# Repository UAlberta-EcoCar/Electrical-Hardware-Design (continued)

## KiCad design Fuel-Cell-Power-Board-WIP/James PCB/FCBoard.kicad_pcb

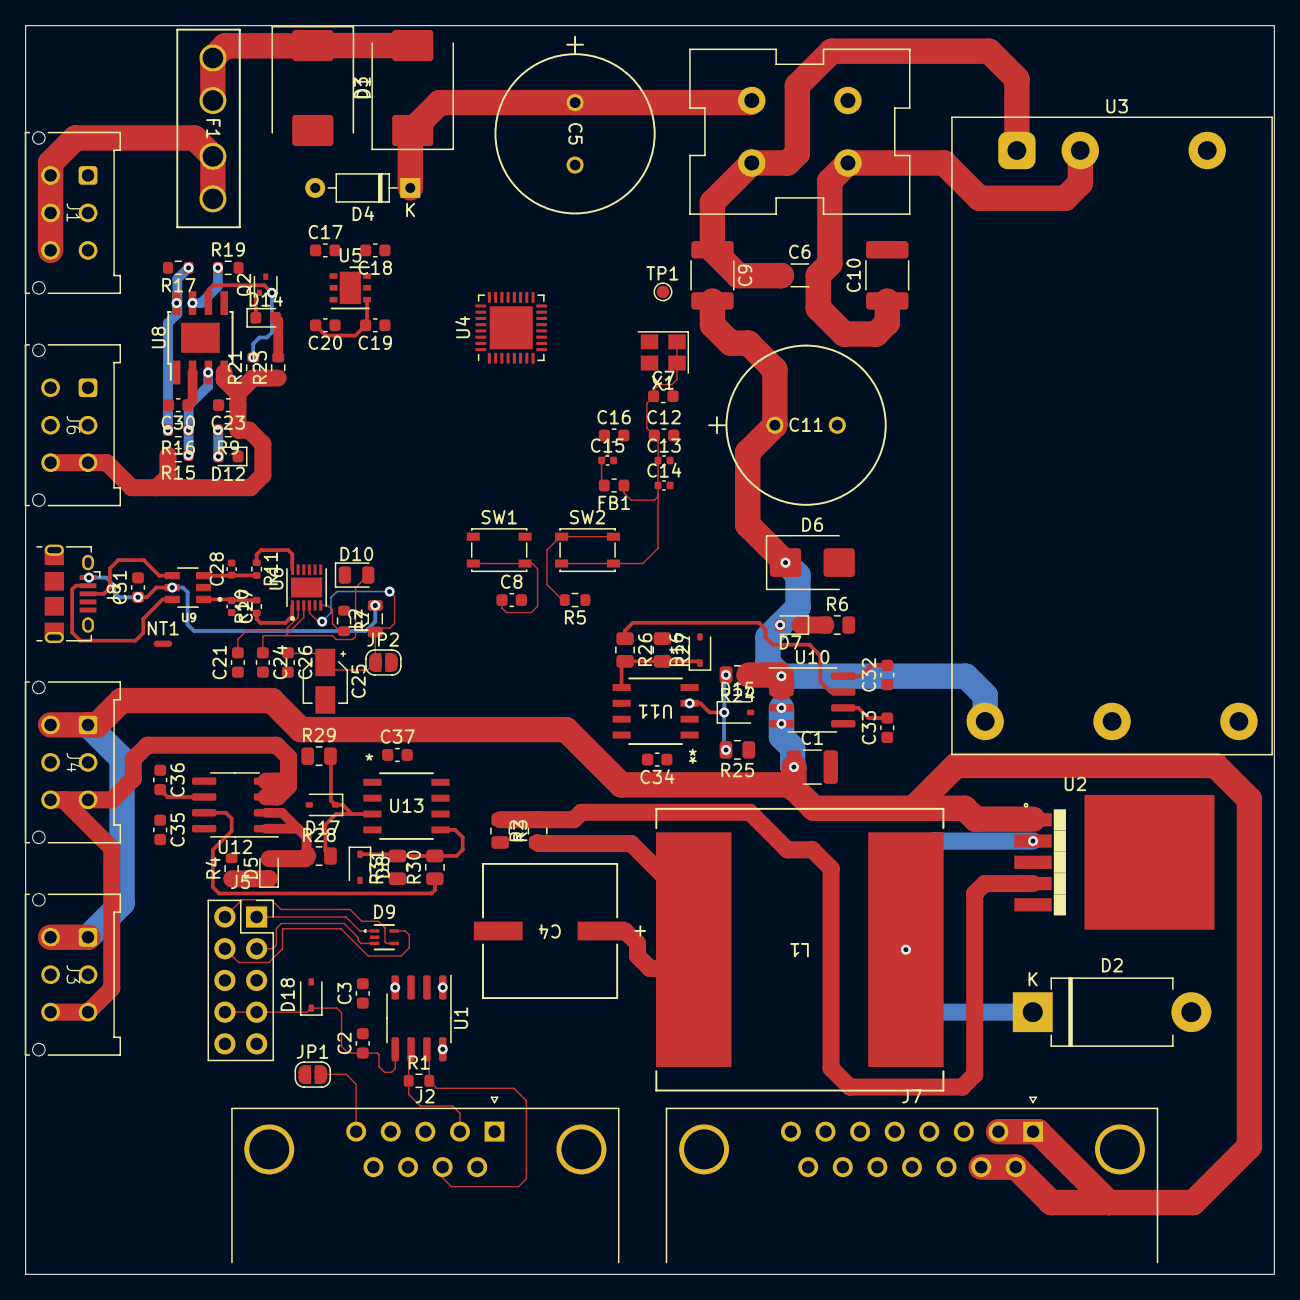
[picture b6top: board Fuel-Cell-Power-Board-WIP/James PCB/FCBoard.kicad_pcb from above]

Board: 4 copper layers, 100.0 x 100.0 mm, 108 parts (0 on the bottom side), 76 nets.

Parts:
C1: 100u; C_1210_3225Metric
C2, C3, C7, C8, C18, C20, C21, C23, C24, C26, C31: 100n; C_0603_1608Metric
C4: 1000u; PCAP_10x10-ELECT_NCA
C5, C11: 100u; CAP_UAQ_12P5X20_NCH
C6: 10u; C_1206_3216Metric
C9, C10: 6.8n; C_1812_4532Metric
C12: 4u7; C_0603_1608Metric
C13, C14, C15: 100n; C_0402_1005Metric
C16, C17, C19: 1u; C_0603_1608Metric
C25: 4u7; CP_Elec_3x5.3
C27, C28: 47p; C_0402_1005Metric
C30: 2n2; C_0603_1608Metric
C32, C34, C35, C37: 0.1u; C_0603_1608Metric
C33, C36: 1n; C_0603_1608Metric
D1: S10ML-TP; D_SMC
D2: 1N5822; D_DO-201AD_P12.70mm_Horizontal
D3: SL44-E3_57T; D_SMC
D4: 1N5255B-TR; D_DO-35_SOD27_P7.62mm_Horizontal
D5, D7: LED; LED_0603_1608Metric
D6: SMBJ12A; D_SMB
D8, D15, D16, D17, D18: MM3Z3V3ST1GOSDKR-ND; D_SOD-323
D9: ESDALC6V1P5
D10: PINK; LED_0805_2012Metric
D12: BLUE; LED_0603_1608Metric
D14: RED; LED_0603_1608Metric
F1: 3544-2; CONN_3544-2_KEY
FB1: 300R; L_0603_1608Metric
FL1: Filter_EMI_LL_1423; CMC
J1, J3, J4, J6: STD_PWR_HEADER
J2: DE9_Receptacle; DSUB-9_Female_Horizontal_P2.77x2.84mm_EdgePinOffset7.70mm_H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
J5: Conn_02x05_Odd_Even; PinSocket_2x05_P2.54mm_Vertical
J7: DA15_Receptacle_MountingHoles; DSUB-15_Female_Horizontal_P2.77x2.84mm_EdgePinOffset7.70mm_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
J8: USB_B_Micro; USB_Micro-B_Amphenol_10118194_Horizontal
JP1, JP2: SolderJumper_2_Open; SolderJumper-2_P1.3mm_Open_RoundedPad1.0x1.5mm
L1: 100u; IND_101M51_VIS
L2: 600R/0.5A; L_0805_2012Metric
NT1: NetTie_2; NetTie-2_SMD_Pad0.5mm
Q2: NMOS; SOT-523
R1: 120; R_0603_1608Metric
R2: 3.1k; R_0805_2012Metric
R3, R25, R27, R29, R31: 1k; R_0805_2012Metric
R4: 560; R_0603_1608Metric
R5, R21: 10k; R_0603_1608Metric
R6, R28: 2k; R_0805_2012Metric
R7: 30.1; R_0603_1608Metric
R9: 150R; R_0603_1608Metric
R10, R11: 26.7; R_0402_1005Metric
R15: 150k; R_0603_1608Metric
R16: 7k87; R_0603_1608Metric
R17: 47k; R_0603_1608Metric
R19: 1k1; R_0603_1608Metric
R23: 120R; R_0603_1608Metric
R24: 2.7k; R_0805_2012Metric
R26, R30: 1.5k; R_0805_2012Metric
SW1, SW2: PTS815 SJM 250 SMTR LFS; SW_SPST_PTS810
TP1: MCO; TestPoint_Pad_D1.0mm
U1: MCP2542FD-E/SN; SOIC-8_3.9x4.9mm_P1.27mm
U2: LM2576D2TR4-5G; D2PAK-5
U3: RPA60-2412SFW; Converter_DCDC_RECOM_RPA60-xxxxSFW
U4: STM32L432KCUx; QFN-32-1EP_5x5mm_P0.5mm_EP3.45x3.45mm
U5: LD39050PU33R; DFN-6-1EP_3x3mm_P0.95mm_EP1.7x2.6mm
U6: FT234XD-R; SON45P300X300X80-13N
U8: TPS2596; TI_SO-PowerPAD-8
U9: USBLC6-2SC6
U10, U12: ACS712xLCTR-05B; SOIC-8_3.9x4.9mm_P1.27mm
U11, U13: TSV912IDT; SO8_STM
X1: OXETDLJANF-8MHZ; Crystal_SMD_3225-4Pin_3.2x2.5mm

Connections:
+5V: C3.2, C17.2, C18.2, C32.2, C34.2, C35.2, C37.1, JP2.2 (B), U1.3 (VDD), U5.1 (EN), U5.6 (VI), U8.5 (OUT), U10.8 (VCC), U11.8 (V+), U12.8 (VCC), U13.8 (V+)
/5V_Current_Meas1: U4.11 (PA5), U13.6 (-), U13.7
/5V_UP: C23.1, J6.3 (5V), J6.6 (5V), R9.1, R15.2, R21.1, R23.1, U8.4 (IN)
/5V_Voltage_Meas1: U4.12 (PA6), U13.1, U13.2 (-)
/12V_Current_Meas: U4.9 (PA3), U11.6 (-), U11.7
/12V_Voltage_Meas: U4.10 (PA4), U11.1, U11.2 (-)
/12V_{FC}: C1.1, J3.1 (12V), J3.4 (12V), J4.1 (12V), J4.4 (12V), J7.1, J7.2, J7.9, J7.10, U2.1 (VIN), U10.3 (IP-), U10.4 (IP-)
/BOOT0: R5.2, SW2.1, U4.31 (PH3)
/CAN_H: J2.7, R1.2, U1.7 (CANH)
/CAN_L: J2.2, R1.1, U1.6 (CANL)
/CAN_{RXD}: U1.4 (RXD), U4.21 (PA11)
/CAN_{STBY}: U1.8 (STBY), U4.25 (PA15)
/CAN_{TXD}: U1.1 (TXD), U4.22 (PA12)
/D+: J8.3 (D+), U9.4
/D-: J8.2 (D-), U9.6
/DM: C27.1, R10.2, U9.1
/DP: C28.1, R11.2, U9.3
/FC+: F1.3, F1.4, J1.4 (12V), J1.5 (GND), J1.6 (5V)
/FC_5V_B1: J3.3 (5V), J3.6 (5V), J4.3 (5V), J4.6 (5V), U12.3 (IP-), U12.4 (IP-)
/FTDI_{~RST}: C21.2, U4.15 (PB1), U6.2 (~RESET#)
/GND_{1}: J8.5 (GND), NT1.2, U9.2
/I_{MON}5V: R19.1, U8.7 (ILM)
/MCU_3V3: C2.1, C7.1, C12.1, C13.1, C14.1, C19.2, C20.2, D18.1 (K), FB1.1, J5.7, J5.8, SW2.2, U1.5 (VIO), U4.1 (VDD), U4.17 (VDD), U5.4 (VO), X1.1 (Tri-State), X1.4 (VDD)
/PA0: U4.6 (PA0), X1.3 (OUT)
/PA1: J7.3, U4.7 (PA1)
/PA2: J7.11 (P111), U4.8 (PA2)
/PA8: TP1.1, U4.18 (PA8)
/PA9: U4.19 (PA9), U6.10 (RXD)
/PA10: U4.20 (PA10), U6.7 (TXD)
/PA13: D9.5, J5.4, U4.23 (PA13)
/PA14: D9.4, J5.2, U4.24 (PA14)
/PB0: J7.4, U4.14 (PB0)
/PB3: U4.26 (PB3), U6.11 (CTS#)
/PB4: U4.27 (PB4), U6.8 (RTS#)
/PB5: J7.12, U4.28 (PB5)
/PB6: J7.5, U4.29 (PB6)
/PB7: J7.13, U4.30 (PB7)
/SHIELD: J2.5, JP1.2 (B)
/SW_{IM}: D9.3, J5.3
/U_5V: J5.9, J5.10
/VCCIO: C24.1, D10.2 (A), U6.3 (3V3OUT), U6.9 (VCCIO)
/V_{BUS}: C31.1, J8.1 (VBUS), L2.2, U9.5
/VoltageCurrentSensing5V_1/Current_Sense_IN: C4.1, D5.2 (A), L1.2, R2.1, R28.1, U12.1 (IP+), U12.2 (IP+)
/VoltageCurrentSensing12V/Current_Sense_IN: C9.2, C11.1, D6.1 (K), D7.2 (A), R24.1, U3.6 (+VOUT), U10.1 (IP+), U10.2 (IP+)
/~FAULT: Q2.2 (G), R21.2, U8.6 (~FAULT)
/~RST: C8.1, D9.1, J5.1, SW1.2, U4.4 (NRST)
GND: C1.2, C2.2, C3.1, C4.2, C7.2, C8.2, C10.2, C11.2, C12.2, C13.2, C14.2, C15.2, C16.2, C17.1, C18.1, C19.1, C20.1, C21.1, C23.2, C24.2, C25.2, C26.2, C27.2, C28.2, C30.2, C31.2, C32.1, C33.1, C34.1, C35.1, C36.1, C37.2, D2.2 (A), D6.2 (A), D8.2 (A), D9.2, D12.1 (K), D15.2 (A), D16.2 (A), D17.2 (A), D18.2 (A), J2.0 (PAD), J2.6, J3.2 (GND), J3.5 (GND), J4.2 (GND), J4.5 (GND), J5.5, J5.6, J6.2 (GND), J6.5 (GND), J7.0 (PAD), J7.7, J7.8, J7.14, J7.15, J8.6 (Shield), JP1.1 (A), NT1.1, Q2.3 (S), R3.2, R4.2, R5.1, R6.2, R17.2, R19.2, R25.1, R27.1, R29.1, R31.1, SW1.1, U1.2 (VSS), U2.3 (GND), U2.5 (ON/OFF), U3.5 (-VOUT), U4.16 (VSS), U4.32 (VSS), U4.33 (VSS), U5.2 (GND), U5.7 (GND), U6.5 (GND), U6.13 (GND__1), U8.1 (GND), U8.9 (PAD), U10.5 (GND), U11.4 (V-), U12.5 (GND), U13.4 (V-), X1.2 (GND)
GND1: C5.2, D1.2 (A), D4.2 (A), FL1.1, J1.1 (12V), J1.2 (GND), J1.3 (5V)
unnamed: D1.1 (K), D3.2 (A), F1.1, F1.2
unnamed: D2.1 (K), L1.1, U2.2 (OUT)
unnamed: C5.1, D3.1 (K), D4.1 (K), FL1.2
unnamed: D5.1 (K), R4.1
unnamed: D7.1 (K), R6.1
unnamed: D8.1 (K), R30.2, R31.2, U13.5 (+)
unnamed: D10.1 (K), R7.1
unnamed: D12.2 (A), R9.2
unnamed: D14.2 (A), R23.2
unnamed: D14.1 (K), Q2.1 (D)
unnamed: D15.1 (K), R24.2, R25.2, U11.3 (+)
unnamed: D16.1 (K), R26.2, R27.2, U11.5 (+)
unnamed: D17.1 (K), R28.2, R29.2, U13.3 (+)
unnamed: C25.1, C26.1, JP2.1 (A), L2.1, U6.4 (VCC)
unnamed: R2.2, R3.1, U2.4 (FB)
unnamed: C6.1, C9.1, FL1.3, U3.1 (+VIN)
unnamed: C6.2, C10.1, FL1.4, U3.2 (-VIN)
unnamed: C15.1, C16.1, FB1.2, U4.5 (VDDA)
unnamed: R7.2, U6.6 (CBUS0)
unnamed: R10.1, U6.1 (USBDM)
unnamed: R11.1, U6.12 (USBDP)
unnamed: R15.1, R16.1, U8.3 (EN/UVLO)
unnamed: R16.2, R17.1, U8.8 (OVLO)
unnamed: C30.1, U8.2 (dV/dT)
unnamed: C33.2, U10.6 (FILTER)
unnamed: R26.1, U10.7 (VIOUT)
unnamed: C36.2, U12.6 (FILTER)
unnamed: R30.1, U12.7 (VIOUT)

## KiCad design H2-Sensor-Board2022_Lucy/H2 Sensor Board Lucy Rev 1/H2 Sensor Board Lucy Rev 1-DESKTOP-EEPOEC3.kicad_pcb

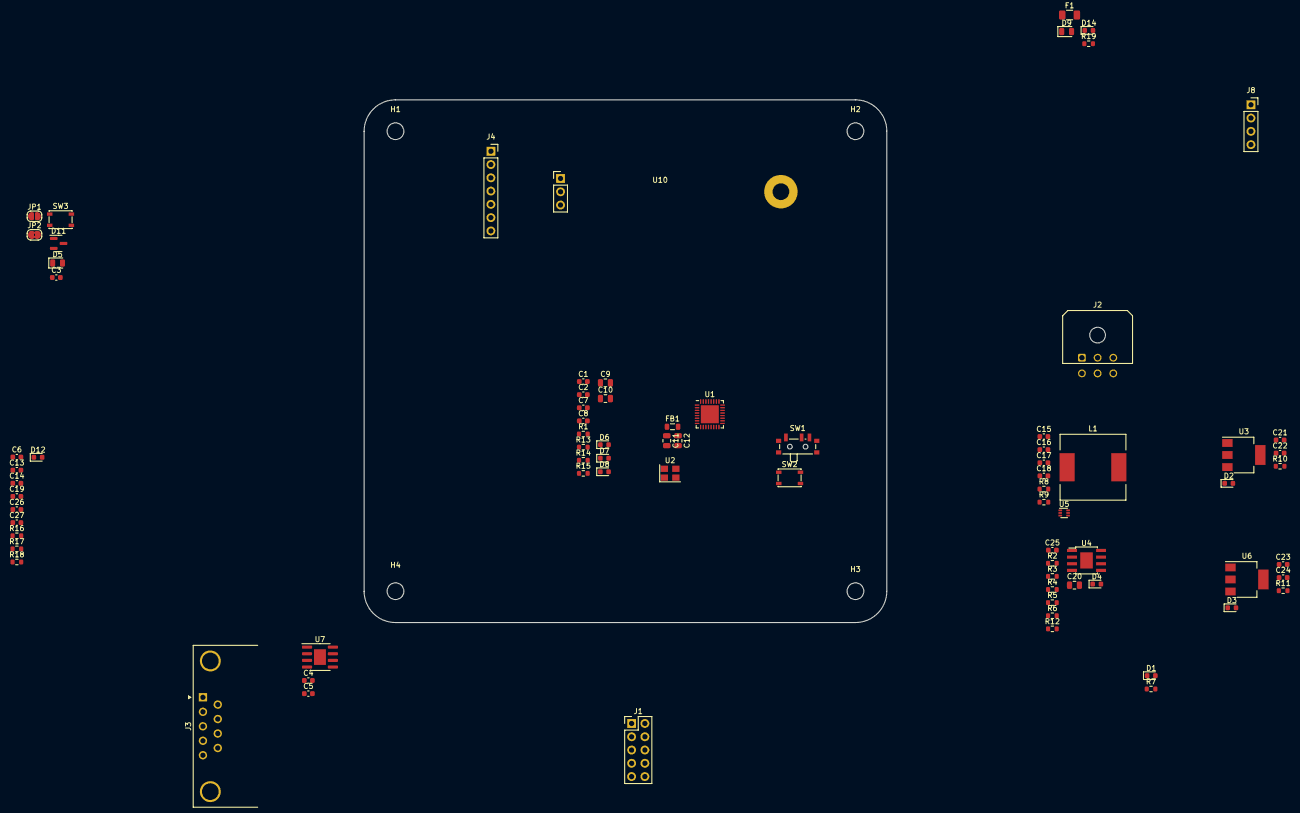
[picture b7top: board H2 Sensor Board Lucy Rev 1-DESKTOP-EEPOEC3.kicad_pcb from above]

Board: 2 copper layers, 100.0 x 100.0 mm, 83 parts (0 on the bottom side), 49 nets, no tracks yet.

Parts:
C1, C2, C3, C4, C5, C6, C7, C8, C14, C18, C27: 100n; C_0603_1608Metric
C9, C10: 10u; C_0805_2012Metric
C11, C12: 1u; C_0805_2012Metric
C13: 4u7; C_0603_1608Metric
C15, C21, C23: 10u; C_0603_1608Metric
C16, C17, C22, C24: 22u; C_0603_1608Metric
C19, C26: 47p; C_0603_1608Metric
C20: 100u; C_0805_2012Metric
C25: 0.1u; C_0603_1608Metric
D1, D6: GREEN; LED_0603_1608Metric
D2, D3, D4, D14: BLUE; LED_0603_1608Metric
D5: D_Zener; D_0805_2012Metric
D7: RED; LED_0603_1608Metric
D8, D12: AMBER; LED_0603_1608Metric
D9: D_Schottky; D_0805_2012Metric
D11: BAT54C; SOT-23
F1: Polyfuse; Fuse_1206_3216Metric
FB1: 600R; L_0805_2012Metric
H1, H2, H3, H4: MountingHole; MountingHole_3.2mm_M3
J1: Conn_02x05_Top_Bottom; PinHeader_2x05_P2.54mm_Vertical
J2: Conn_02x03_Top_Bottom; Molex_Micro-Fit_3.0_43045-0600_2x03_P3.00mm_Horizontal
J3: Conn_01x09_Socket; DSUB-9_Female_Horizontal_P2.77x2.84mm_EdgePinOffset7.70mm_H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
J4: SHT31D Module; PinSocket_1x07_P2.54mm_Vertical
J8: OLED; PinSocket_1x04_P2.54mm_Vertical
JP1: Address 0x45; SolderJumper-2_P1.3mm_Open_RoundedPad1.0x1.5mm
JP2: Address 0x44; SolderJumper-2_P1.3mm_Bridged2Bar_RoundedPad1.0x1.5mm
L1: 2.2u; L_12x12mm_H8mm
R1, R9: 10k; R_0603_1608Metric
R2: 464; R_0603_1608Metric
R3: 1k5; R_0603_1608Metric
R4: 47k; R_0603_1608Metric
R5: 13k; R_0603_1608Metric
R6: 450k; R_0603_1608Metric
R7, R10, R11, R12, R19: 600R; R_0603_1608Metric
R8: 77.5k; R_0603_1608Metric
R13, R14, R15: 100; R_0603_1608Metric
R16: 260R; R_0603_1608Metric
R17, R18: 27R; R_0603_1608Metric
SW1: SW_SPDT; SW_SPDT_PCM12
SW2: RESET; SW_SPST_PTS810
SW3: TARE; SW_SPST_PTS810
U1: STM32L432KCUx; QFN-32-1EP_5x5mm_P0.5mm_EP3.45x3.45mm
U2: 8MHz; Crystal_SMD_3225-4Pin_3.2x2.5mm
U3: AZ1117H-5.0; SOT-223-3_TabPin2
U4: TPS2596; TI_SO-PowerPAD-8
U5: AP62250Z6; SOT-563
U6: AZ1117EH-3.3; SOT-223-3_TabPin2
U7: MCP2542FD-E/SN; SOIC-8-1EP_3.9x4.9mm_P1.27mm_EP2.29x3mm
U10: H2_Sensor_Daughter_Board_Rev_1

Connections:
+3.3V: C7.1, C8.1, C9.1, SW1.3 (C), U1.1 (VDD), U1.17 (VDD)
+3.3VA: C10.1, C11.1, FB1.1, U1.5 (VDDA)
+3V3: C1.2, C5.2, C6.1, C24.1, D12.2 (A), J1.1, R11.1, U2.1 (~ST), U2.4 (VCC), U6.2 (VO), U7.5 (VIO)
+5V: C4.2, C13.1, C14.1, C22.1, C23.1, D11.1, J4.7, J8.2, JP1.2 (B), R10.1, U3.2 (VO), U6.3 (VI), U7.3 (VDD)
+12V: C15.1, C20.1, U4.5 (OUT), U5.1 (VIN), U5.5 (EN)
/BOOT0: R1.2, U1.31 (PH3)
/CAN_RX: U1.21 (PA11), U7.4 (RXD)
/CAN_STBY: U1.3 (PC15), U7.8 (STBY)
/CAN_TX: U1.22 (PA12), U7.1 (TXD)
/CD+: J3.7, U7.7 (CANH)
/CD-: J3.2, U7.6 (CANL)
/DEBUG_SWDIO: J1.2, U1.23 (PA13)
/DEBUG_SWO: J1.6, U1.26 (PB3)
/GPLED1: R15.2, U1.11 (PA5)
/GPLED2: R14.2, U1.12 (PA6)
/GPLED3: R13.2, U1.13 (PA7)
/H2_Sense: D5.1 (K), U1.7 (PA1)
/NRST: C2.2, J1.10, SW2.2, U1.4 (NRST)
/Power/5V_UP: J2.3, J2.6, R3.2, R7.1
/Power/7V: C16.1, C17.1, C21.1, L1.2, R8.1, U3.3 (VI)
/Power/12V_UP: C25.1, J2.1, J2.4, R6.2, R12.1, U4.4 (IN)
/Power/I_{MON}: R2.1, U4.7 (ILM)
/Power/~FAULT: R3.1, U4.6 (~FAULT)
/TARE: C3.2, SW3.2, U1.28 (PB5)
/XCLK: U1.6 (PA0), U2.3 (OUT)
GND: C1.1, C2.1, C3.1, C4.1, C5.1, C6.2, C7.2, C8.2, C9.2, C10.2, C11.2, C12.2, C13.2, C14.2, C15.2, C16.2, C17.2, C19.1, C20.2, C21.2, C22.2, C23.2, C24.2, C25.2, C26.1, C27.1, D2.1 (K), D3.1 (K), D4.1 (K), D5.2 (A), D6.1 (K), D7.1 (K), D8.1 (K), D14.1 (K), J1.3, J1.5, J1.9, J2.2, J2.5, J4.6, J8.1, JP2.1 (A), R4.2, R9.1, SW1.1 (A), SW2.1, SW3.1, U1.16 (VSS), U1.32 (VSS), U1.33 (VSS), U2.2 (GND), U3.1 (GND), U4.1 (GND), U4.2 (dV/dT), U4.9 (PAD), U5.3 (GND), U6.1 (GND), U7.2 (VSS), U7.9 (VSS), U10.1 (GND)
unnamed: C12.1, FB1.2
unnamed: C19.2, R17.2
unnamed: C26.2, R18.2
unnamed: D1.2 (A), R7.2
unnamed: D2.2 (A), R10.2
unnamed: D3.2 (A), R11.2
unnamed: D4.2 (A), R12.2
unnamed: D6.2 (A), R13.1
unnamed: D7.2 (A), R14.1
unnamed: D8.2 (A), R15.1
unnamed: D9.2 (A), R19.1
unnamed: D9.1 (K), F1.1
unnamed: D12.1 (K), R16.2
unnamed: D14.2 (A), R19.2
unnamed: J4.3, JP1.1 (A), JP2.2 (B)
unnamed: R1.1, SW1.2 (B)
unnamed: R5.1, R6.1, U4.3 (EN/UVLO)
unnamed: R4.1, R5.2, U4.8 (OVLO)
unnamed: C18.2, U5.4 (BST)
unnamed: R8.2, R9.2, U5.6 (FB)
unnamed: C18.1, L1.1, U5.2 (SW)
unnamed: D11.3, U10.3 (V_HEAT)
V_HEAT: D11.2, F1.2
